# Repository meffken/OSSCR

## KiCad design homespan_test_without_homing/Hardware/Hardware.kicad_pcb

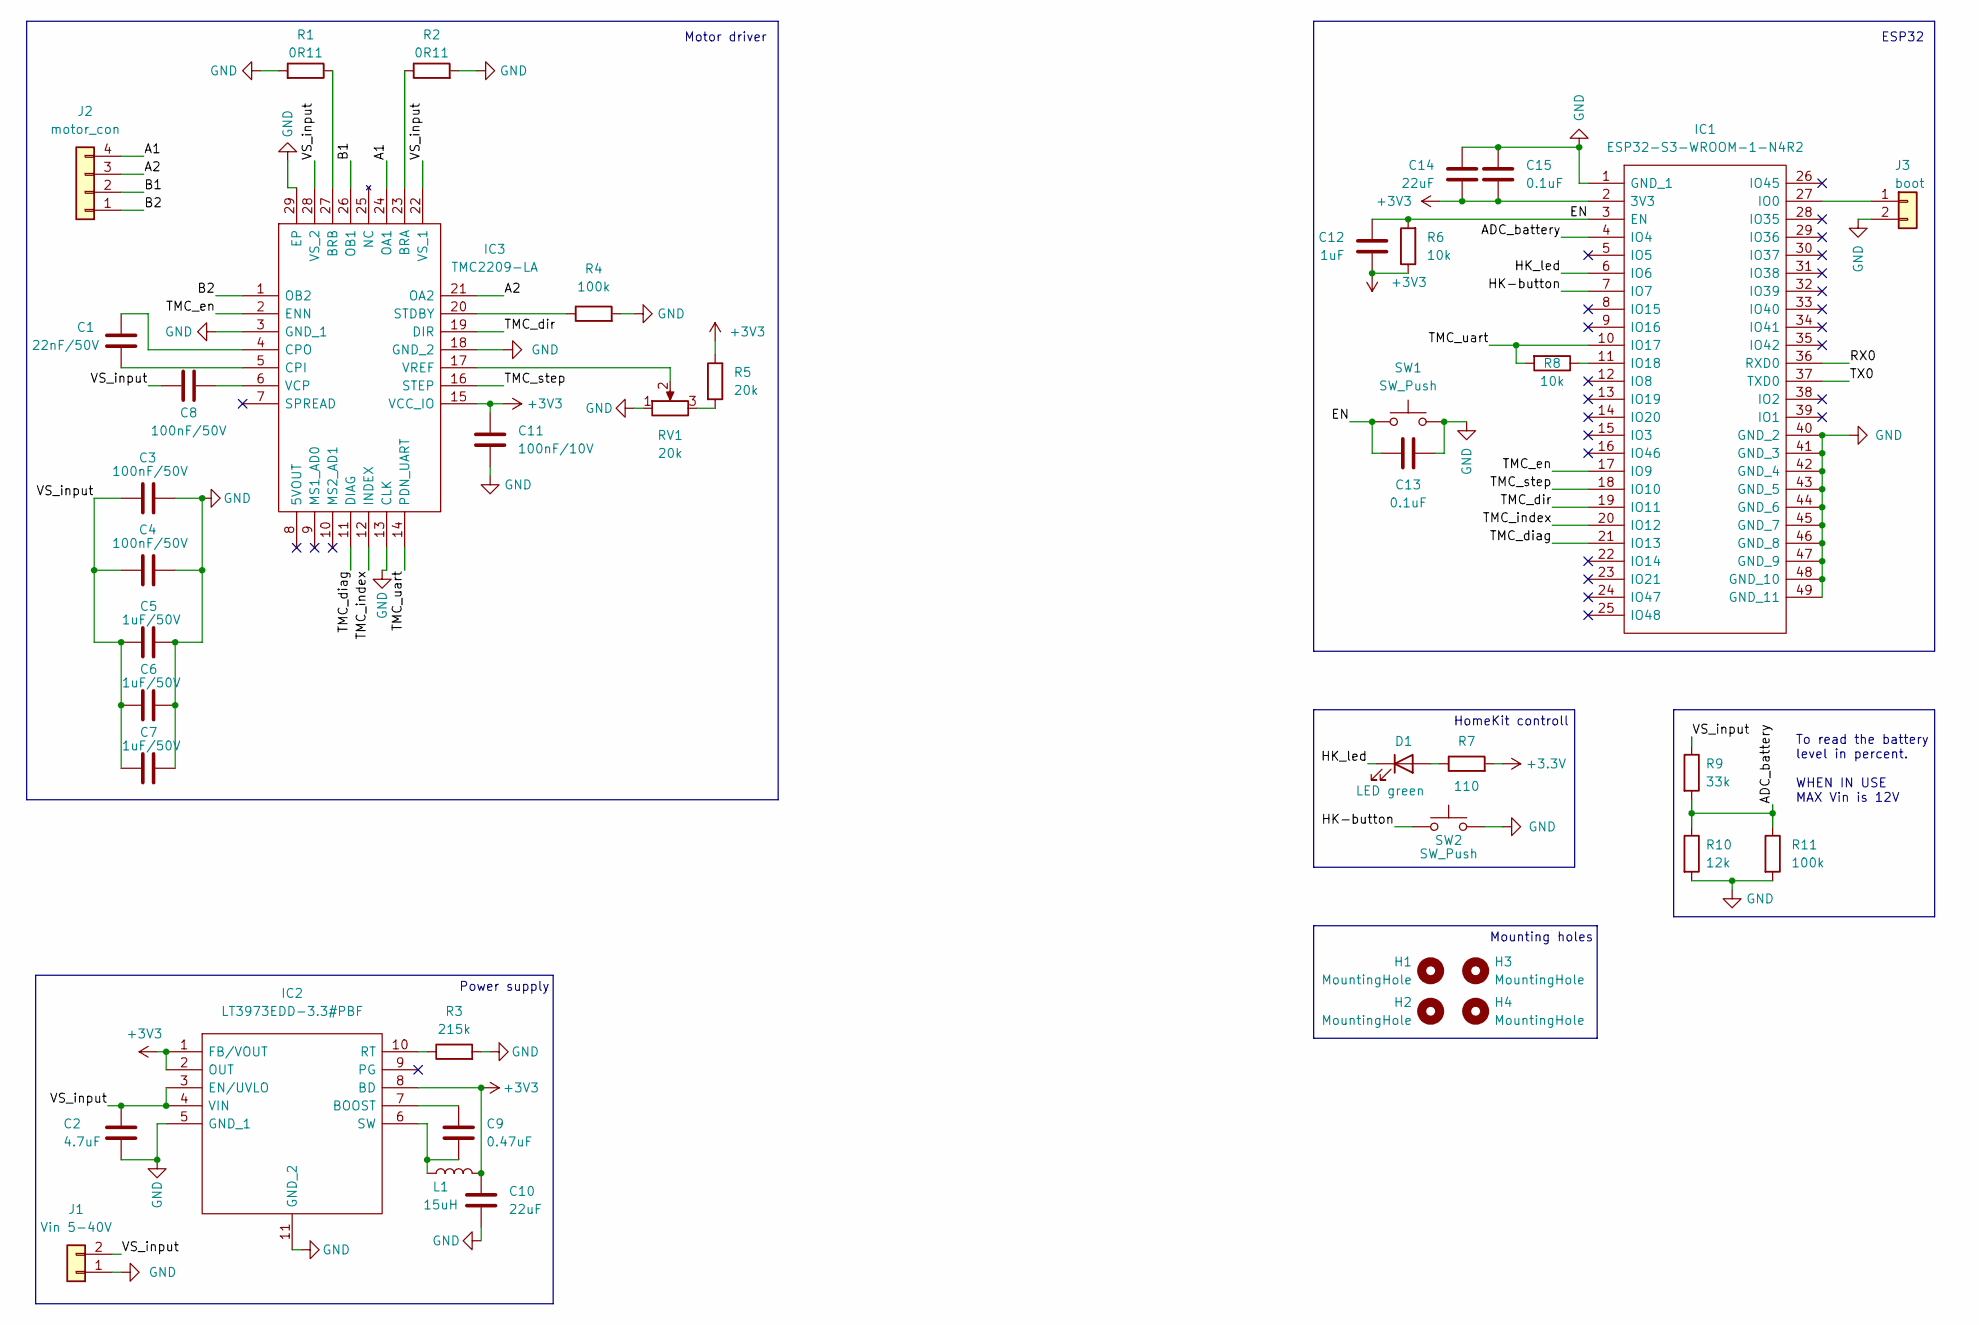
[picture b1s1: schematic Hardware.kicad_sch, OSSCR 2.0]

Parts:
C1: 22nF/50V; C_0805_2012Metric
C2: 4.7uF; C_0805_2012Metric
C3, C4, C8: 100nF/50V; C_0805_2012Metric
C5, C6, C7: 1uF/50V; C_0805_2012Metric
C9: 0.47uF; C_0805_2012Metric
C10, C14: 22uF; C_0805_2012Metric
C11: 100nF/10V; C_0805_2012Metric
C12: 1uF; C_0805_2012Metric
C13, C15: 0.1uF; C_0805_2012Metric
D1: LED green; LED_0603_1608Metric
H1, H2, H3, H4: MountingHole; MountingHole_3.2mm_M3
IC1: ESP32-S3-WROOM-1-N4R2; ESP32S3WROOM1N4R2; Mouser Part Number 356-ESP32S3WROM1N4R2
IC2: LT3973EDD-3.3#PBF; SON50P300X300X80-11N-D; Mouser Part Number 584-LT3973EDD-3.3PBF
IC3: TMC2209-LA; QFN50P500X500X90-29N; Mouser Part Number 700-TMC2209-LA
J1: Vin 5-40V; JST_XH_B2B-XH-A_1x02_P2.50mm_Vertical
J2: motor_con; JST_XH_B4B-XH-A_1x04_P2.50mm_Vertical
J3: boot; PinHeader_1x02_P2.54mm_Vertical
L1: 15uH; L_0805_2012Metric
R1, R2: 0R11; R_2010_5025Metric
R3: 215k; R_0603_1608Metric
R4, R11: 100k; R_0603_1608Metric
R5: 20k; R_0603_1608Metric
R6, R8: 10k; R_0603_1608Metric
R7: 110; R_0603_1608Metric
R9: 33k; R_0603_1608Metric
R10: 12k; R_0603_1608Metric
RV1: 20k; Potentiometer_ACP_CA6-VSMD_Vertical_Hole
SW1, SW2: SW_Push; SW_SPST_B3U-1000P-B

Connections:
/A1: IC3.24 (OA1), J2.4
/A2: IC3.21 (OA2), J2.3
/ADC_battery: IC1.4 (IO4), R9.2, R10.1, R11.1
/B1: IC3.26 (OB1), J2.2
/B2: IC3.1 (OB2), J2.1
/EN: C12.2, C13.1, IC1.3 (EN), R6.2, SW1.1
/HK-button: IC1.7 (IO7), SW2.1
/HK_led: D1.1 (K), IC1.6 (IO6)
/RX0: IC1.36 (RXD0)
/TMC_diag: IC1.21 (IO13), IC3.11 (DIAG)
/TMC_dir: IC1.19 (IO11), IC3.19 (DIR)
/TMC_en: IC1.17 (IO9), IC3.2 (ENN)
/TMC_index: IC1.20 (IO12), IC3.12 (INDEX)
/TMC_step: IC1.18 (IO10), IC3.16 (STEP)
/TMC_uart: IC1.10 (IO17), IC3.14 (PDN_UART), R8.2
/TX0: IC1.37 (TXD0)
/VS_input: C2.2, C3.1, C4.1, C5.2, C6.2, C7.2, C8.2, IC2.3 (EN/UVLO), IC2.4 (VIN), IC3.22 (VS_1), IC3.28 (VS_2), J1.2, R9.1
GND: C2.1, C3.2, C4.2, C5.1, C6.1, C7.1, C10.1, C11.2, C13.2, C14.2, C15.1, IC1.1 (GND_1), IC1.40 (GND_2), IC1.41 (GND_3), IC1.42 (GND_4), IC1.43 (GND_5), IC1.44 (GND_6), IC1.45 (GND_7), IC1.46 (GND_8), IC1.47 (GND_9), IC1.48 (GND_10), IC1.49 (GND_11), IC2.5 (GND_1), IC2.11 (GND_2), IC3.3 (GND_1), IC3.13 (CLK), IC3.18 (GND_2), IC3.29 (EP), J1.1, J3.2, R1.2, R2.2, R3.2, R4.2, R10.2, R11.2, RV1.1, SW1.2, SW2.2
unnamed: C1.1, IC3.4 (CPO)
unnamed: C1.2, IC3.5 (CPI)
unnamed: C8.1, IC3.6 (VCP)
unnamed: C9.1, IC2.7 (BOOST)
unnamed: C9.2, IC2.6 (SW), L1.1
unnamed: D1.2 (A), R7.1
unnamed: IC1.11 (IO18), R8.1
unnamed: IC1.27 (IO0), J3.1
unnamed: IC2.10 (RT), R3.1
unnamed: IC3.17 (VREF), RV1.2
unnamed: IC3.20 (STDBY), R4.1
unnamed: IC3.23 (BRA), R2.1
unnamed: IC3.27 (BRB), R1.1
unnamed: R5.2, RV1.3

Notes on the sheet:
To read the battery level in percent. WHEN IN USE MAX Vin is 12V
ESP32
HomeKit controll
Mounting holes
Power supply
Motor driver

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
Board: 2 copper layers, 41 parts (14 on the bottom side), 31 nets, no tracks yet.

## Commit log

2022-05-13 smal improvements
2022-05-14 minor bug fixes
2022-05-22 smal chanches
2022-05-29 add hardware
2022-06-02 add board
2022-06-03 add pcb
2022-06-03 add reference run
